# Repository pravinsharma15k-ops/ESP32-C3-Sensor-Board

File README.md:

# ESP32-C3 Sensor Board

A compact, battery-powered IoT sensor board built around the **ESP32-C3-WROOM-02** module. It combines environment, light and sound sensing with USB-C charging, a built-in USB-to-UART bridge (auto-program), external flash and a microSD card slot.

Designed in **KiCad 10.0.6** as a 4-layer PCB.

---

## Features

- **MCU:** ESP32-C3-WROOM-02 (Wi-Fi + Bluetooth LE, RISC-V)
- **Power:** USB-C input with fuse, Li-Po charging (MCP73871), 3.3 V LDO (LM1117-3.3)
- **USB-UART:** CP2102N (QFN-20) with USBLC6-2SC6 ESD protection
- **Auto-program:** DTR/RTS transistor circuit (2x BC817) for automatic BOOT/EN control, no manual button press needed to flash
- **Sensors:**
  - BME280: temperature, humidity, pressure (I2C)
  - TEMT6000: ambient light sensor
  - CMC-5042PF-AC electret microphone with MAX4466 amplifier
- **Storage:** W25Q32JV 32 Mbit SPI flash and microSD card slot
- **User interface:** BOOT and RESET buttons, I2C OLED header, GPIO breakout header
- **Indicators:** power, charging, charged and power-good LEDs, plus UART status LEDs
- **Test points:** TP1 to TP5 for SPI signals (MOSI, MISO, SCLK, CS, CS_CD)
- **PCB:** 4 layers, antenna keep-out zone, fully routed (0 unrouted nets)

---

## Block Overview

| Block | Main parts |
|---|---|
| USB-C input | J1 (SS-52400-003), F1 fuse, 5.1k CC resistors |
| Battery charger | U1 MCP73871, J2 JST-PH battery connector |
| Voltage regulator | VR1 LM1117MPX-3.3 |
| MCU | U3 ESP32-C3-WROOM-02 |
| USB to UART | U4 CP2102N, U5 USBLC6-2SC6 |
| Flash memory | U6 W25Q32JVSSIQ |
| SD card | J3 GSD090012SEU |
| Environment sensor | U2 BME280 |
| Light sensor | Q1 TEMT6000X01 |
| Microphone | MK1 CMC-5042PF-AC + U7 MAX4466EXK |
| Boot / reset | S1 (BOOT), S2 (RESET), Q2/Q3 BC817 |
| Headers | J4 (OLED, 4-pin I2C), J5 (breakout: GPIO8, GPIO18, GPIO19, 3.3 V, GND) |

---

## Components List

Values are taken from the schematic.

### Sheet 1: Power (root)

| Ref | Component | Value / Part number |
|---|---|---|
| J1 | USB-C connector | SS-52400-003 |
| F1 | Fuse | 0ZCH0110AF2E |
| J2 | Battery connector (JST-PH) | B2B-PH-SM4-TB |
| U1 | Li-Po charger | MCP73871 |
| VR1 | 3.3 V LDO regulator | LM1117MPX-3.3 |
| LED1, LED4 | Red LEDs | LTST-C170KRKT |
| LED2, LED3 | Green LEDs | LTST-C170GKT |
| C1, C2, C5 | Capacitors | 0.1 uF |
| C3, C4 | Capacitors | 10 uF |
| C6 | Capacitor | 1 uF |
| R1, R2 | Resistors | 10 k |
| R3, R4 | Resistors (USB-C CC) | 5.1 k |
| R5 | Resistor | 2 k |
| R6 | Resistor | 20 k |
| R7, R8, R9, R10 | Resistors (LED) | 470 |

### Sheet 2: ESP32-C3, USB-UART, flash, SD card

| Ref | Component | Value / Part number |
|---|---|---|
| U3 | Wi-Fi + BLE module | ESP32-C3-WROOM-02 |
| U4 | USB-to-UART bridge | CP2102N-Axx-xQFN20 |
| U5 | USB ESD protection | USBLC6-2SC6 |
| U6 | SPI flash (32 Mbit) | W25Q32JVSSIQ |
| J3 | microSD card slot | GSD090012SEU |
| TP1 to TP5 | Test points | MOSI, MISO, SCLK, CS, CS_CD |
| LED5 | Red LED | LTST-C170KRKT |
| LED6 | Green LED | LTST-C170GKT |
| C7, C9, C12 | Capacitors | 10 uF |
| C8, C10, C132, C133 | Capacitors | 0.1 uF |
| C11 | Capacitor | 1 uF |
| R11 | Resistor | 1 k |
| R12 | Resistor | 22.1 k |
| R13 | Resistor | 47.5 k |
| R14, R18 | Resistors (LED) | 470 |
| R15, R16, R20, R22 | Resistors | 50 |
| R19 | Resistor | 10 k |

### Sheet 3: Sensors

| Ref | Component | Value / Part number |
|---|---|---|
| U2 | Temperature, humidity, pressure sensor | BME280 |
| Q1 | Ambient light sensor | TEMT6000X01 |
| U7 | Microphone amplifier | MAX4466EXK |
| MK1 | Electret microphone | CMC-5042PF-AC |
| C15, C16, C18, C20 | Capacitors | 0.1 uF |
| C17 | Capacitor | 10 uF |
| C19 | Capacitor | 1 uF |
| R23, R30 | Resistors | 10 k |
| R24, R25 | Resistors (I2C pull-up) | 4.7 k |
| R26, R28 | Resistors | 2 k |
| R27, R29 | Resistors | 1 M |
| R31 | Resistor | 100 k |

### Sheet 4: User interface

| Ref | Component | Value / Part number |
|---|---|---|
| J4 | OLED display header (I2C) | Conn_01x04_Pin |
| J5 | GPIO breakout header | Conn_01x05_Pin |
| S1 | BOOT button | Tactile switch |
| S2 | RESET button | Tactile switch |
| Q2, Q3 | Auto-program transistors | BC817 |
| R32, R33, R34 | Resistors | 10 k |
| C21 | Capacitor | 0.1 uF |
| C22 | Capacitor | 1 uF |

---

## Schematic Structure

The design is hierarchical (4 sheets):

| Sheet | File | Content |
|---|---|---|
| 1/4 | `ESP32-project.kicad_sch` | Root: power input, charger, regulator, LEDs |
| 2/4 | `esp32-c3-02.kicad_sch` | ESP32-C3, USB-UART, flash, SD card, test points |
| 3/4 | `sensors.kicad_sch` | BME280, photo sensor, microphone and amplifier |
| 4/4 | `user_intertface.kicad_sch` | OLED header, BOOT/RESET buttons, auto-program, breakout |

Full schematic PDF: [`ESP32-project.pdf`](ESP32-project/ESP32-project.pdf)

---

## Power Path

```
USB-C (5 V) -> Fuse -> MCP73871 -> Li-Po battery (JST-PH)
                          |
                          +-> +5V rail -> LM1117-3.3 -> +3.3 V (ESP32, sensors, flash, SD)
```

The MCP73871 supports power-path management, so the board runs from USB while the battery charges.

---

## Programming

1. Connect the board to your PC with a USB-C cable.
2. The CP2102N appears as a serial port.
3. Flash using Arduino IDE, ESP-IDF or PlatformIO. The DTR/RTS circuit puts the ESP32-C3 into boot mode automatically.
4. For manual boot mode: hold **BOOT**, press **RESET**, release both.

Reference: [ESP32 boot mode selection](https://docs.espressif.com/projects/esptool/en/latest/esp32c3/advanced-topics/boot-mode-selection.html)

---

## PCB Details

| Item | Value |
|---|---|
| EDA tool | KiCad 10.0.6 |
| Layers | 4 (F.Cu, In1.Cu, In2.Cu, B.Cu) |
| Pads | 330 |
| Vias | 145 |
| Nets | 76 |
| Unrouted | 0 |
| Antenna | Keep-out zone at the board edge, no copper or components under the ESP32 antenna |

Silkscreen includes the Open Source Hardware logo, ESD warning symbol and section labels (REG, USB, SOUND, LIGHT, FLASH, BOOT).

---

## PCB Layers

### Copper layers (4-layer stackup)

| Layer | Name | Purpose |
|---|---|---|
| 1 | **F.Cu** (top) | Components and signal routing (red) |
| 2 | **In1.Cu** | Internal layer: copper plane (zone fill) with some routing |
| 3 | **In2.Cu** | Internal layer: copper plane (zone fill) with some routing |
| 4 | **B.Cu** (bottom) | Signal routing (blue) |

### Other layers used

| Layer | Purpose |
|---|---|
| F.Silkscreen / B.Silkscreen | Reference designators, section labels, logos (Open Hardware, ESD, KiCad logo on back) |
| F.Mask / B.Mask | Solder mask openings for pads |
| F.Paste / B.Paste | Solder paste stencil for SMD pads |
| F.Courtyard / B.Courtyard | Component keep-out area for placement |
| F.Fab / B.Fab | Fabrication outlines of parts |
| Edge.Cuts | Board outline |
| User.Drawings / User.Comments | Antenna keep-out zone and notes |

---

## Board Preview

| 3D view (top) | PCB layout |
|:---:|:---:|
|  |  |

- **Board:** 4-layer, 330 pads, 145 vias, 783 track segments, 76 nets, 0 unrouted
- **Antenna:** 5 mm keep-out zone at the top right, no copper or parts
- **Placement:** ESP32-C3 module top right, microSD slot bottom right, USB-C bottom centre, JST-PH battery connector bottom left, sensors and microphone on the left

## PCB Layer Views

| Component layout |
|:---:|
|  |

- **F.Cu / B.Cu:** red tracks on top, blue tracks on bottom; the thick red track carries power from the charger towards the regulator
- **In1.Cu:** copper pour (green) with a few tracks, no pour under the antenna
- **In2.Cu:** copper pour (orange) with some routing, cutout around the USB-C connector area
- **Silkscreen:** reference designators, section labels (REG, SOUND, LIGHT, FLASH, USB, BOOT), header pin labels, ESD symbol, Open Source Hardware logo; the mirrored KiCad logo is on the back
- **Component layout:** pads in purple and courtyards in magenta with tracks hidden

## Schematic

The schematic has four sections:

1. **Root:** USB-C input, fuse, MCP73871 Li-Po charger, LM1117-3.3 regulator, status LEDs, JST-PH battery connector
2. **ESP32-C3:** ESP32-C3-WROOM-02, CP2102N USB-UART, USBLC6-2SC6 ESD protection, W25Q32JV flash, microSD slot, test points
3. **Sensors:** BME280, TEMT6000 light sensor, electret microphone with MAX4466 amplifier
4. **User interface:** I2C OLED header, GPIO breakout header, BOOT and RESET buttons, DTR/RTS auto-program transistors

| Sheet 1: Root | Sheet 2: ESP32-C3 |
|:---:|:---:|
|  |  |

| Sheet 3: Sensors | Sheet 4: User interface |
|:---:|:---:|
|  |  |

---

## Repository Structure

```
ESP32-project
├── ESP32-project.kicad_pro
├── ESP32-project.kicad_sch        # root sheet
├── esp32-c3-02.kicad_sch
├── sensors.kicad_sch
├── user_intertface.kicad_sch
├── ESP32-project.kicad_pcb
├── ESP32-project.pdf              # schematic
├── image/                       
├── README.md
└── Project_library
    ├── 3D-model/                   # STEP models
    ├── footprint.pretty/           # Footprint files
    └── symbol/                     # Symbol files
```

> Adjust the file names to match your repository.

---

## Getting Started

1. Install [KiCad 10](https://www.kicad.org/download/).
2. Clone the repository:
   ```bash
   git clone https://github.com/pravinsharma15k-ops/<repo-name>.git
   ```
3. Open `ESP32-project.kicad_pro`.
4. Make sure the custom symbol, footprint and 3D model library paths are set (Preferences > Manage Symbol/Footprint Libraries, and Configure Paths for 3D models).

---

## Status

- [x] Schematic complete (v2.0)
- [x] PCB layout and routing complete
- [x] 3D models check for all parts
- [ ] Prototype fabrication
- [ ] Firmware and testing

---

## Author

**Pravin Kumar Sharma**
B.Tech ECE, RIT Roorkee

- GitHub: [pravinsharma15k-ops](https://github.com/pravinsharma15k-ops)
- LinkedIn: [pravin-sharma-ece](https://linkedin.com/in/pravin-sharma-ece)

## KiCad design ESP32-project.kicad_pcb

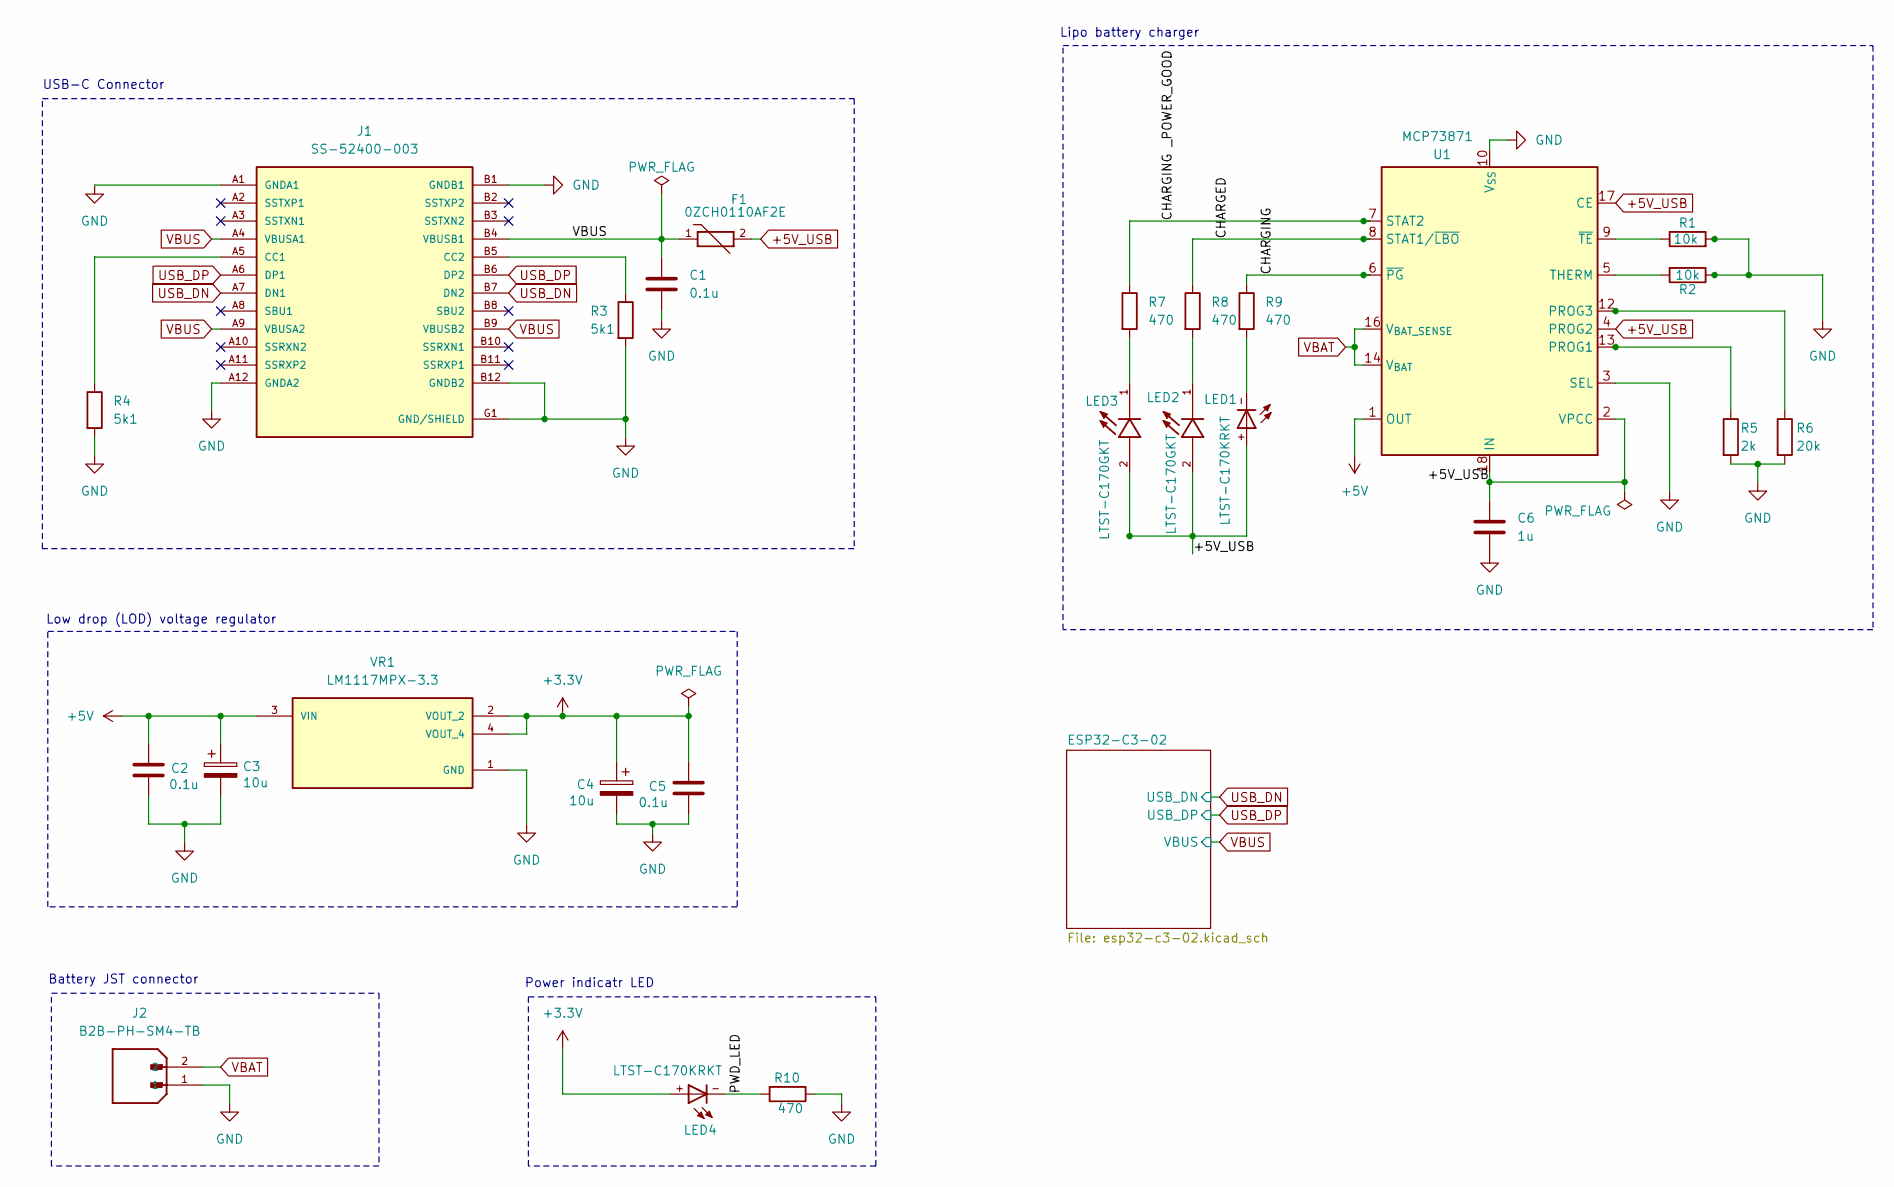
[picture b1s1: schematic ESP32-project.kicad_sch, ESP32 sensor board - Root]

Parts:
C1, C2, C5: 0.1u; C_0805_2012Metric
C3, C4: 10u; T491A106K010AT
C6: 1u; C_0805_2012Metric
F1: 0ZCH0110AF2E; FUSC3225X100N; PARTREV Apr2023
J1: SS-52400-003; BELFUSE_SS-52400-003; PARTREV A0
J2: B2B-PH-SM4-TB; JST_B2B-PH-SM4-TB; PARTREV N/A
LED1, LED4: LTST-C170KRKT; DIOC200X125X110
LED2, LED3: LTST-C170GKT; LED_LTST-C170GKT; PARTREV I
R1, R2: 10k; R_0805_2012Metric
R3, R4: 5k1; R_0805_2012Metric
R5: 2k; R_0805_2012Metric
R6: 20k; R_0805_2012Metric
R7, R8, R9, R10: 470; R_0805_2012Metric
U1: MCP73871; QFN-20-1EP_5x5mm_P0.65mm_EP3.35x3.35mm
VR1: LM1117MPX-3.3; VREG_LM1117MPX-3.3; PARTREV O

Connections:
+3.3V: C4.1, C5.1, LED4.+, VR1.2 (VOUT_2), VR1.4 (VOUT_4); also elsewhere on the board
+5V: C2.1, C3.1, U1.1 (OUT), U1.20 (OUT), VR1.3 (VIN)
+5V_USB: C6.1, F1.2, LED1.+, LED2.2, LED3.2, U1.2 (VPCC), U1.4 (PROG2), U1.17 (CE), U1.18 (IN), U1.19 (IN)
/CHARGED: R8.1, U1.8 (STAT1/~LBO)
/CHARGING: R9.1, U1.6 (~PG)
/CHARGING _POWER_GOOD: R7.1, U1.7 (STAT2)
/PWD_LED: LED4.-, R10.2
GND: C1.2, C2.2, C3.2, C4.2, C5.2, C6.2, J1.A1 (GNDA1), J1.A12 (GNDA2), J1.B1 (GNDB1), J1.B12 (GNDB2), J1.G1 (GND/SHIELD), J1.G2 (GND/SHIELD), J1.G3 (GND/SHIELD), J1.G4 (GND/SHIELD), J1.S1 (GND/SHIELD), J1.S2 (GND/SHIELD), J1.S3 (GND/SHIELD), J1.S4 (GND/SHIELD), J2.1, R1.2, R2.1, R3.2, R4.2, R5.2, R6.2, R10.1, U1.3 (SEL), U1.10 (V_{SS}), U1.11 (V_{SS}), U1.21 (V_{SS}), VR1.1 (GND); also elsewhere on the board
unnamed: J1.A5 (CC1), R4.1
unnamed: J1.B5 (CC2), R3.1
unnamed: LED1.-, R9.2
unnamed: LED2.1, R8.2
unnamed: LED3.1, R7.2
unnamed: R5.1, U1.13 (PROG1)
unnamed: R6.1, U1.12 (PROG3)
unnamed: R2.2, U1.5 (THERM)
unnamed: R1.1, U1.9 (~TE)
USB_DN: J1.A7 (DN1), J1.B7 (DN2); also elsewhere on the board
USB_DP: J1.A6 (DP1), J1.B6 (DP2); also elsewhere on the board
VBAT: J2.2, U1.14 (V_{BAT}), U1.15 (V_{BAT}), U1.16 (V_{BAT_SENSE})
VBUS: C1.1, F1.1, J1.A4 (VBUSA1), J1.A9 (VBUSA2), J1.B4 (VBUSB1), J1.B9 (VBUSB2); also elsewhere on the board

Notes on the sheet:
Power indicatr LED
USB-C Connector
Battery JST connector
Low drop (LOD) voltage regulator
Lipo battery charger

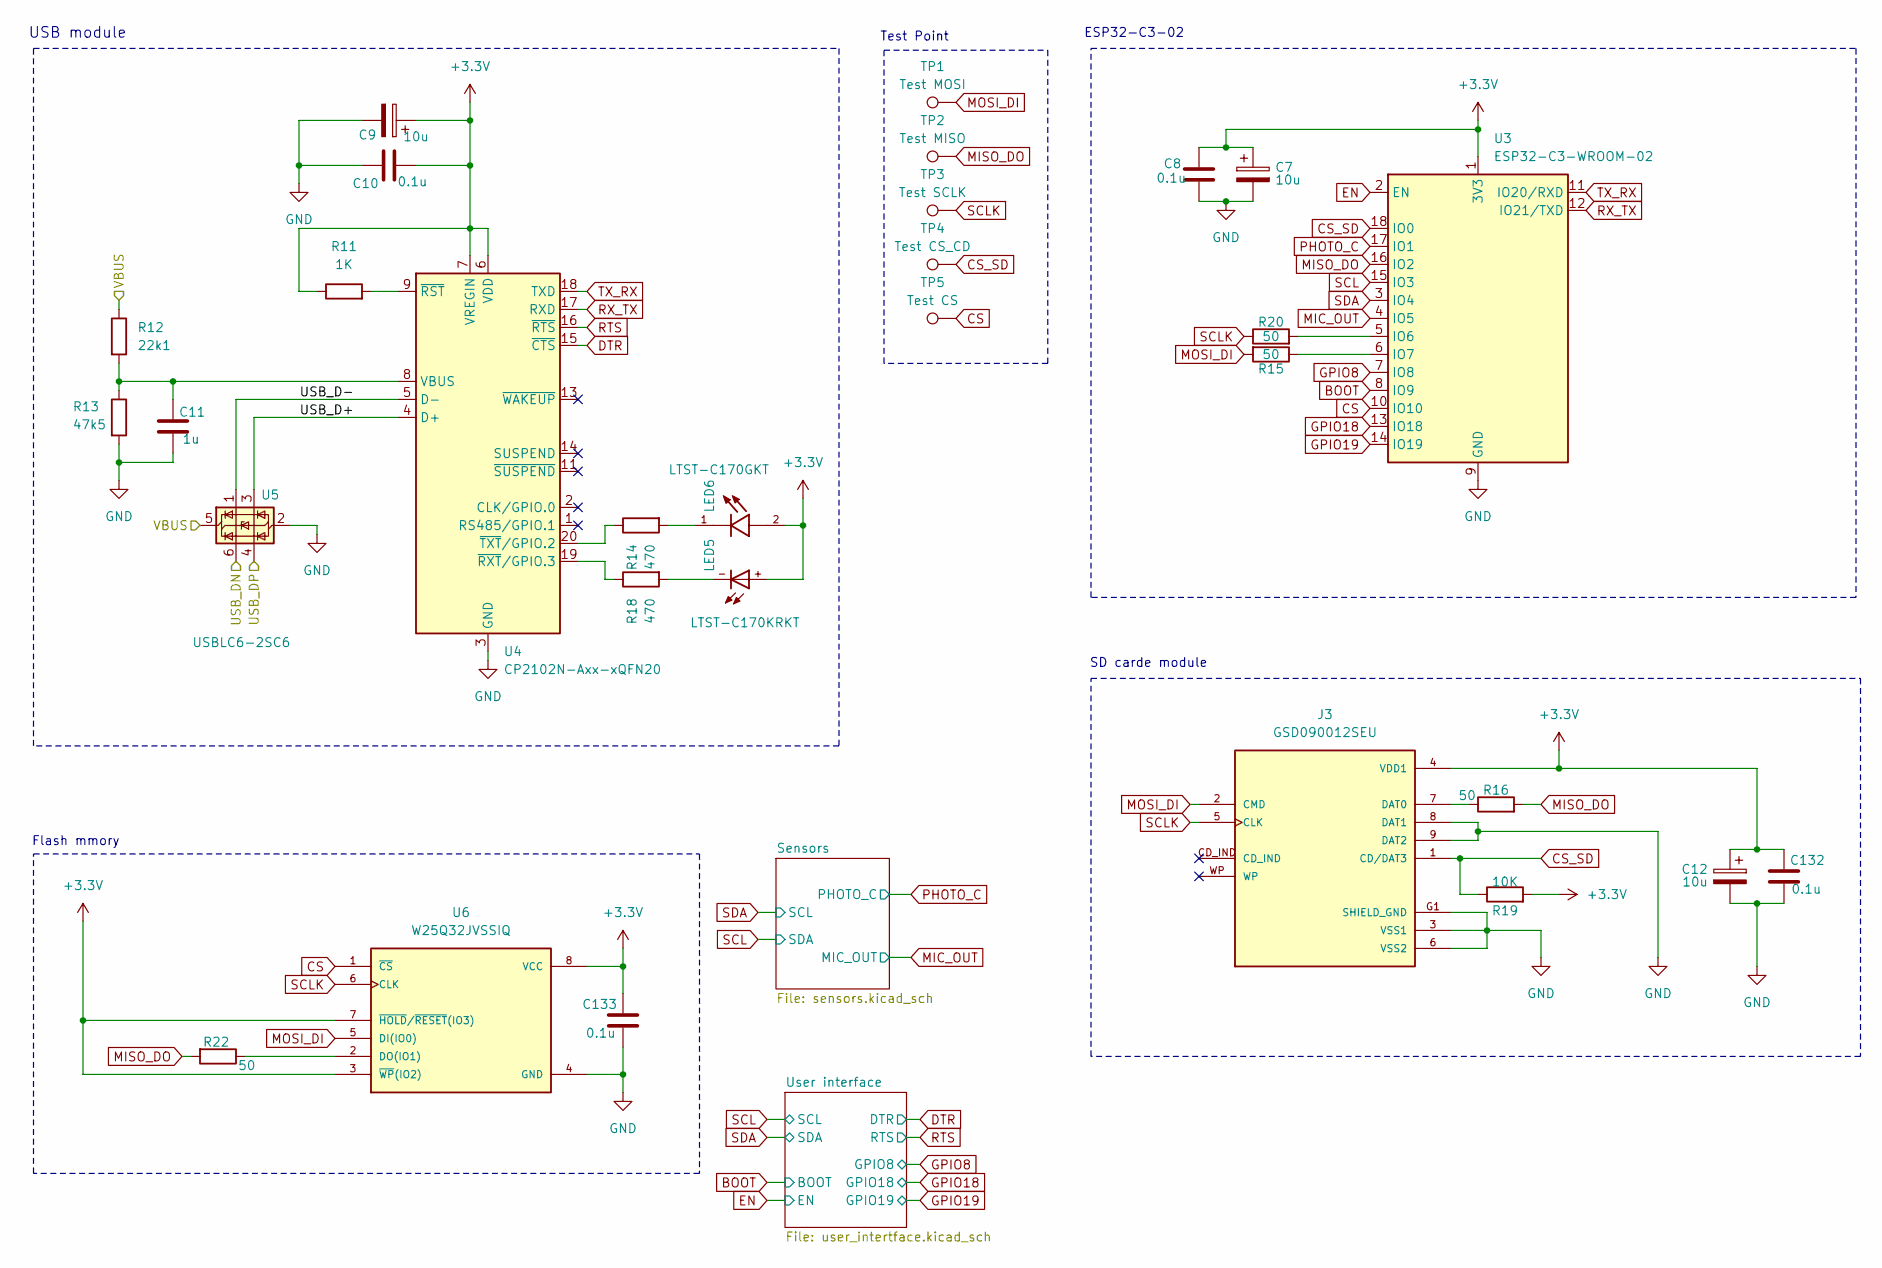
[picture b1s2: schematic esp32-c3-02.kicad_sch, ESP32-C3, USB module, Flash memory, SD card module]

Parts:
C7, C9, C12: 10u; T491A106K010AT
C8, C10, C132, C133: 0.1u; C_0805_2012Metric
C11: 1u; C_0805_2012Metric
J3: GSD090012SEU; AMPHENOL_GSD090012SEU; PARTREV E
LED5: LTST-C170KRKT; DIOC200X125X110
LED6: LTST-C170GKT; LED_LTST-C170GKT; PARTREV I
R11: 1K; R_0805_2012Metric
R12: 22k1; R_0805_2012Metric
R13: 47k5; R_0805_2012Metric
R14, R18: 470; R_0805_2012Metric
R15, R16, R20, R22: 50; R_0805_2012Metric
R19: 10K; R_0805_2012Metric
TP1: Test MOSI; TestPoint_Pad_D1.0mm
TP2: Test MISO; TestPoint_Pad_D1.0mm
TP3: Test SCLK; TestPoint_Pad_D1.0mm
TP4: Test CS_CD; TestPoint_Pad_D1.0mm
TP5: Test CS; TestPoint_Pad_D1.0mm
U3: ESP32-C3-WROOM-02
U4: CP2102N-Axx-xQFN20; SiliconLabs_QFN-20-1EP_3x3mm_P0.5mm_EP1.8x1.8mm
U5: USBLC6-2SC6; SOT-23-6
U6: W25Q32JVSSIQ; SOIC127P790X216-8N; M_PART_NUMBER W25QXX

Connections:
+3.3V: C7.1, C8.2, C9.1, C10.2, C12.1, C132.2, C133.2, J3.4 (VDD1), LED5.+, LED6.2, R11.1, R19.2, U3.1 (3V3), U4.6 (VDD), U4.7 (VREGIN), U6.3 (~WP(IO2)), U6.7 (~HOLD/~RESET(IO3)), U6.8 (VCC); also elsewhere on the board
/ESP32-C3-02/USB_D+: U4.4 (D+), U5.3 (I/O2)
/ESP32-C3-02/USB_D-: U4.5 (D-), U5.1 (I/O1)
BOOT: U3.8 (IO9); also elsewhere on the board
CS: TP5.1 (1_1), U3.10 (IO10), U6.1 (~CS)
CS_SD: J3.1 (CD/DAT3), R19.1, TP4.1 (1_1), U3.18 (IO0)
DTR: U4.15 (~CTS); also elsewhere on the board
EN: U3.2 (EN); also elsewhere on the board
GND: C7.2, C8.1, C9.2, C10.1, C11.2, C12.2, C132.1, C133.1, J3.3 (VSS1), J3.6 (VSS2), J3.8 (DAT1), J3.9 (DAT2), J3.G1 (SHIELD_GND), J3.G2 (SHIELD_GND), J3.G3 (SHIELD_GND), J3.G4 (SHIELD_GND), R13.2, U3.9 (GND), U3.19 (GND), U4.3 (GND), U4.12 (GND), U4.21 (GND), U5.2 (GND), U6.4 (GND); also elsewhere on the board
GPIO8: U3.7 (IO8); also elsewhere on the board
GPIO18: U3.13 (IO18); also elsewhere on the board
GPIO19: U3.14 (IO19); also elsewhere on the board
MIC_OUT: U3.4 (IO5); also elsewhere on the board
MISO_DO: R16.2, R22.2, TP2.1 (1_1), U3.16 (IO2)
MOSI_DI: J3.2 (CMD), R15.2, TP1.1 (1_1), U6.5 (DI(IO0))
unnamed: J3.7 (DAT0), R16.1
unnamed: LED5.-, R18.2
unnamed: LED6.1, R14.2
unnamed: R20.2, U3.5 (IO6)
unnamed: R15.1, U3.6 (IO7)
unnamed: C11.1, R12.2, R13.1, U4.8 (VBUS)
unnamed: R11.2, U4.9 (~RST)
unnamed: R18.1, U4.19 (~RXT/GPIO.3)
unnamed: R14.1, U4.20 (~TXT/GPIO.2)
unnamed: R22.1, U6.2 (DO(IO1))
PHOTO_C: U3.17 (IO1); also elsewhere on the board
RTS: U4.16 (~RTS); also elsewhere on the board
RX_TX: U3.12 (IO21/TXD), U4.17 (RXD)
SCL: U3.15 (IO3); also elsewhere on the board
SCLK: J3.5 (CLK), R20.1, TP3.1 (1_1), U6.6 (CLK)
SDA: U3.3 (IO4); also elsewhere on the board
TX_RX: U3.11 (IO20/RXD), U4.18 (TXD)
USB_DN: U5.6 (I/O1); also elsewhere on the board
USB_DP: U5.4 (I/O2); also elsewhere on the board
VBUS: R12.1, U5.5 (VBUS); also elsewhere on the board

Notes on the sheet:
ESP32-C3-02
USB module
Flash mmory
Test Point
SD carde module

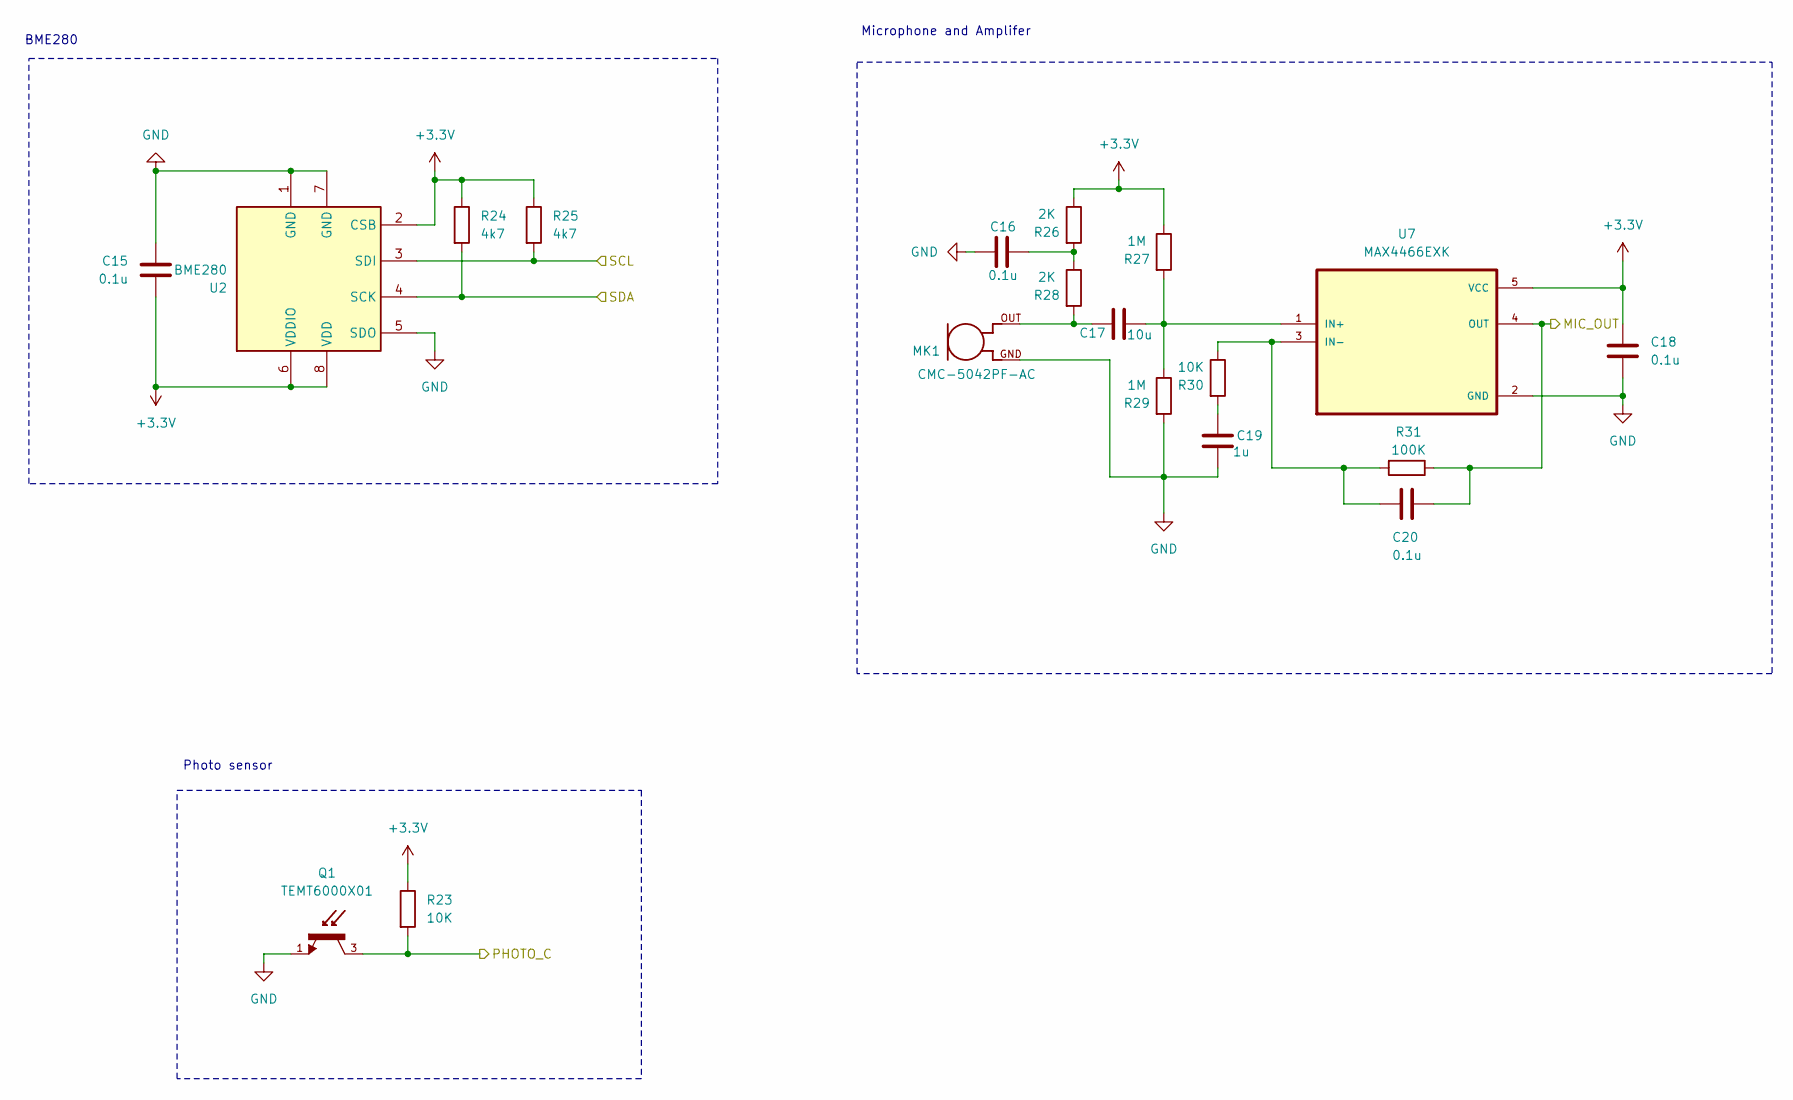
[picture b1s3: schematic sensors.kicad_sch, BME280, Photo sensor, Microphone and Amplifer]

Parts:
C15, C16, C18, C20: 0.1u; C_0805_2012Metric
C17: 10u; C_0805_2012Metric
C19: 1u; C_0805_2012Metric
MK1: CMC-5042PF-AC; CUI_CMC-5042PF-AC
Q1: TEMT6000X01; TRANS_TEMT6000X01; PARTREV 1.9
R23, R30: 10K; R_0805_2012Metric
R24, R25: 4k7; R_0805_2012Metric
R26, R28: 2K; R_0805_2012Metric
R27, R29: 1M; R_0805_2012Metric
R31: 100K; R_0805_2012Metric
U2: BME280; Bosch_LGA-8_2.5x2.5mm_P0.65mm_ClockwisePinNumbering
U7: MAX4466EXK; SOT65P210X110-5N

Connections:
+3.3V: C15.2, C18.1, R23.1, R24.1, R25.1, R26.1, R27.1, U2.2 (CSB), U2.6 (VDDIO), U2.8 (VDD), U7.5 (VCC); also elsewhere on the board
GND: C15.1, C16.2, C18.2, C19.2, MK1.GND, Q1.1, R29.2, U2.1 (GND), U2.5 (SDO), U2.7 (GND), U7.2 (GND); also elsewhere on the board
MIC_OUT: C20.1, R31.1, U7.4 (OUT); also elsewhere on the board
unnamed: C16.1, R26.2, R28.1
unnamed: C17.1, MK1.OUT, R28.2
unnamed: C19.1, R30.2
unnamed: C17.2, R27.2, R29.1, U7.1 (IN+)
unnamed: C20.2, R30.1, R31.2, U7.3 (IN-)
PHOTO_C: Q1.3, R23.2; also elsewhere on the board
SCL: R24.2, U2.4 (SCK); also elsewhere on the board
SDA: R25.2, U2.3 (SDI); also elsewhere on the board

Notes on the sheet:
BME280
Microphone and Amplifer
Photo sensor

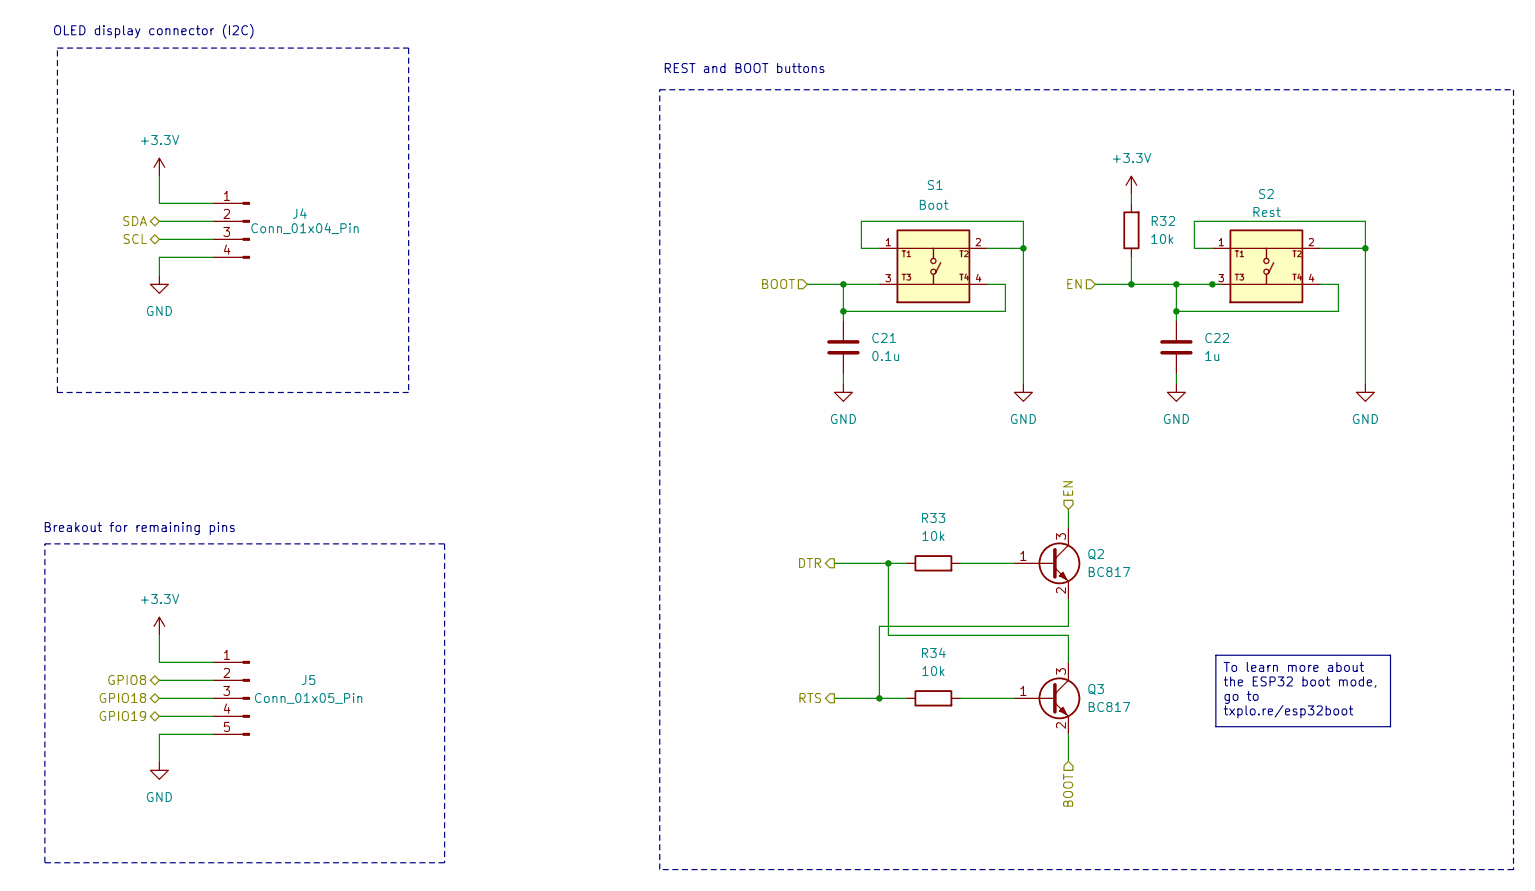
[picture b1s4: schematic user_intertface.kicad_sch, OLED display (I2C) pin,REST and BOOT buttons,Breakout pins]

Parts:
C21: 0.1u; C_0805_2012Metric
C22: 1u; C_0805_2012Metric
J4: Conn_01x04_Pin; PinHeader_1x04_P2.54mm_Vertical
J5: Conn_01x05_Pin; PinHeader_1x05_P2.54mm_Vertical
Q2, Q3: BC817; SOT-23
R32, R33, R34: 10k; R_0805_2012Metric
S1: Boot; SW_USLPT2819DT2TR; PARTREV P
S2: Rest; SW_USLPT2819DT2TR; PARTREV P

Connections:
+3.3V: J4.1, J5.1, R32.2; also elsewhere on the board
BOOT: C21.1, Q3.2 (E), S1.3, S1.4; also elsewhere on the board
DTR: Q3.3 (C), R33.1; also elsewhere on the board
EN: C22.1, Q2.3 (C), R32.1, S2.3, S2.4; also elsewhere on the board
GND: C21.2, C22.2, J4.4, J5.5, S1.1, S1.2, S2.1, S2.2; also elsewhere on the board
GPIO8: J5.2; also elsewhere on the board
GPIO18: J5.3; also elsewhere on the board
GPIO19: J5.4; also elsewhere on the board
unnamed: Q2.1 (B), R33.2
unnamed: Q3.1 (B), R34.2
RTS: Q2.2 (E), R34.1; also elsewhere on the board
SCL: J4.3; also elsewhere on the board
SDA: J4.2; also elsewhere on the board

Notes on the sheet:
OLED display connector (I2C)
REST and BOOT buttons
Breakout for remaining pins
To learn more about the ESP32 boot mode, go to txplo.re/esp32boot

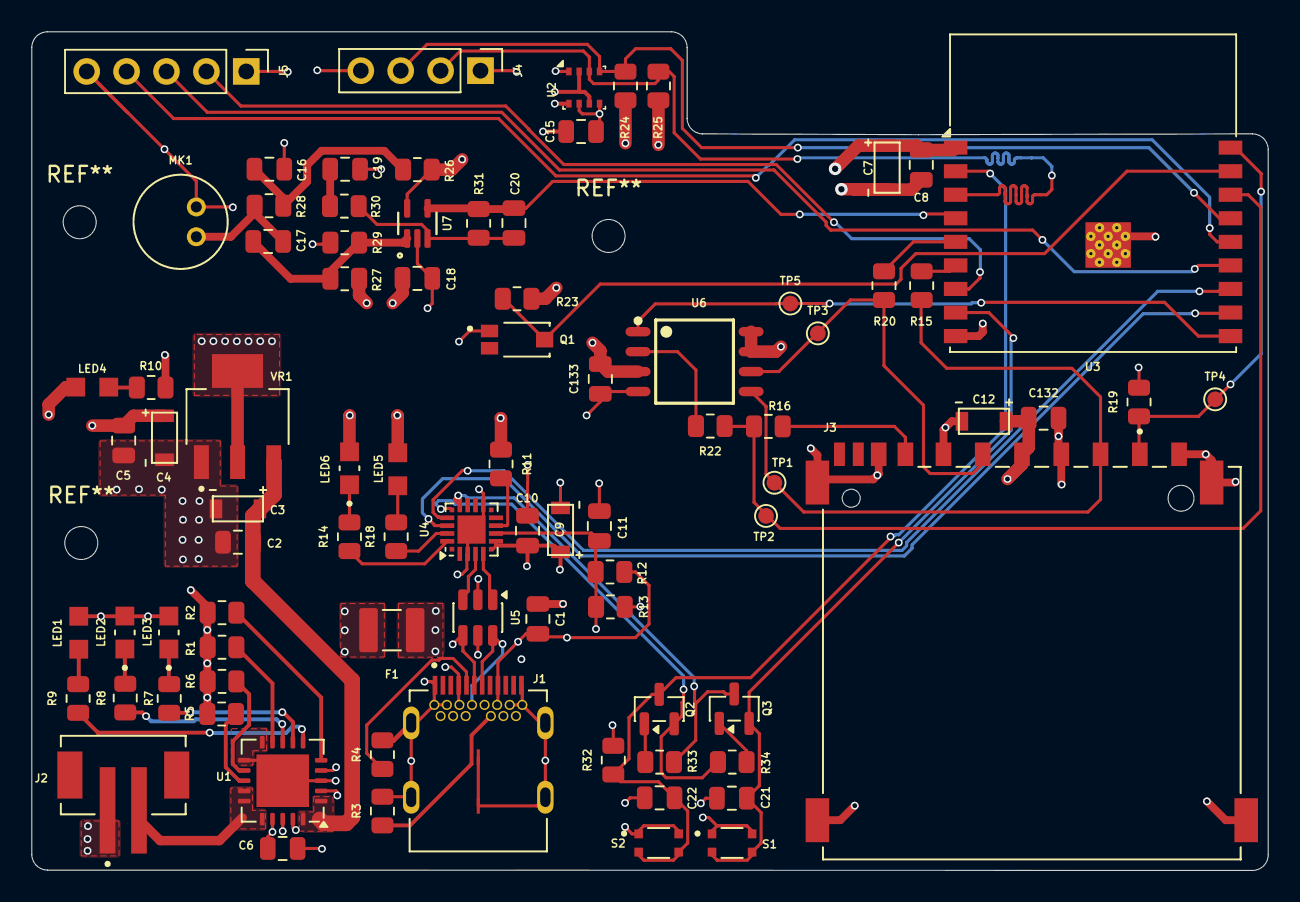
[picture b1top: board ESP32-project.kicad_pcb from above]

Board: 4 copper layers, 78.7 x 53.4 mm, 85 parts (0 on the bottom side), 58 nets.
